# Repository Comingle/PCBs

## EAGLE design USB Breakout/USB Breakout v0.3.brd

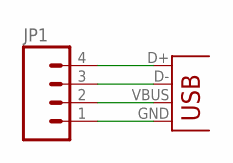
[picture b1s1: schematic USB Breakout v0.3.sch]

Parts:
JP1: M04LONGPADS; 1X04_LONGPADS
JP2: USB-A-SMD; USB-A-S-NOSILK-FEMALE

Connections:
3V3: JP1.2, JP2.VBUS
GND: JP1.1, JP2.GND
IN0: JP1.4, JP2.D+
IN1: JP1.3, JP2.D-

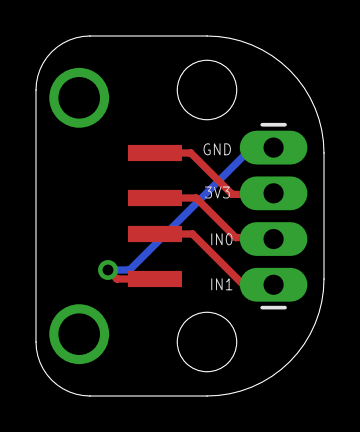
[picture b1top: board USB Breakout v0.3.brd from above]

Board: 2 copper layers, 16.0 x 20.0 mm, 4 parts (0 on the bottom side), 4 nets.

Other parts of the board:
U$1, U$2: STAND-OFF

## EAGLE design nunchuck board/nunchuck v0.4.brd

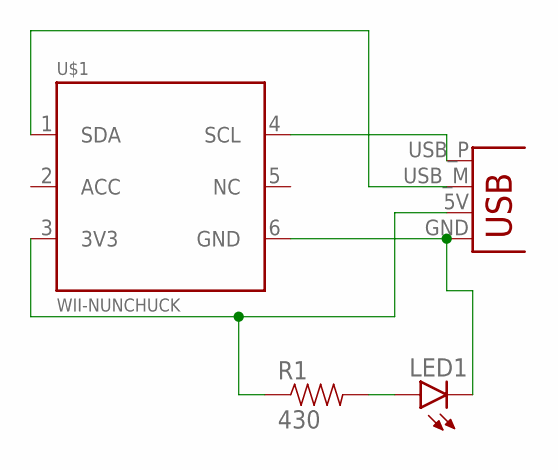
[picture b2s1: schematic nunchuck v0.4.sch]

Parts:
JP1: USBPCB; USB-A-PCB
LED1: LED0603; LED-0603
R1: 430; 0603-RES
U$1: WII-NUNCHUCK; WII_6PIN

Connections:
unnamed: JP1.GND, LED1.C, U$1.6 (GND)
unnamed: JP1.5V (VBUS), R1.1, U$1.3 (3V3)
unnamed: JP1.USB_M (D-), U$1.1 (SDA)
unnamed: JP1.USB_P (D+), U$1.4 (SCL)
unnamed: LED1.A, R1.2

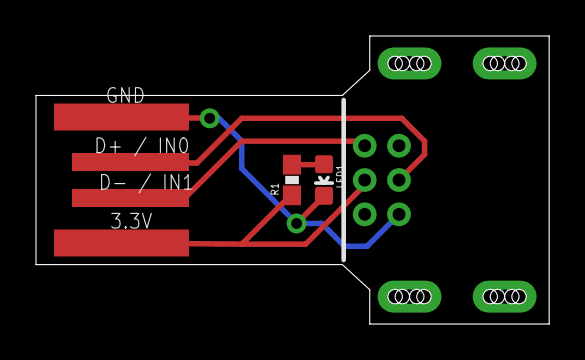
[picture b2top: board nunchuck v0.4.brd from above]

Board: 2 copper layers, 28.5 x 16.0 mm, 4 parts (0 on the bottom side), 5 nets.

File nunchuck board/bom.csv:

"Qty";"Value";"Device";"Package";"Parts";"Description";"";
"1";"USBPCB";"USBPCB";"USB-A-PCB";"JP1";"USB Connectors";"";
"1";"WII-NUNCHUCK";"WII-NUNCHUCK";"WII_6PIN";"U$1";"";"";

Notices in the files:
parts and their libraries:
SparkFun-Connectors: Licensing: Creative Commons ShareAlike 4.0 International - https://creativecommons.org/licenses/by-sa/4.0
